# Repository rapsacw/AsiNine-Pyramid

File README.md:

# aSiNine Pyramid<br>
Schematic and layout in Eagle PCB for a quad bm1387 standalone miner<br>
// skip if deemed off topic!<br>
// Other versions made<br>
// A single BM1391 version, obsolete as information on the asic is too scarce<br>
// aSiNine Pharaonis: dual BM1387 version, compatible with the quad version (this)<br>
// Unnamed project single BM1397 (in pre-alpha stage, pcb's are on the slow boat from China)<br>
<br>
Motivation:
I'm running an ESP32C3 with a RGB LED to monitor traffic (flickers on inbound TX's and glows on memory pool size) to my node.<br>
Why not let it do something useful while idle?<br>
<br>
Properties (concept):
- Standalone miner to be connected to a mining pool or a private Bitcoin node that will serve the work (over websocket)
- Size: 80x60mm
- Programmable Vcore for the bm1387 asics
- ws2812 led for special effects ;)
- max. power usage targeted at ~10-15W
- Cooling: M.2 SSD cooler, tie-wrapped to the board with 5V fan.
- Low(est) cost possible!

Major parts used:
- 4x BM1387xx asics (tested bm1387bf & bm1387b)
- ESP32-C3-mini-1
- SY8208A or B step down regulator (8A) <s>(currently controlled by PWM, considering a cheap ($0.10) DAC)</s> controlled by a dac.
- XC6206P-18 lin. regulators for 1.8 & 0.8V
- SY8009B step down regulator (overkill) for the esp32c3, limiting the power supply to 5V only..
- usb-c connector for power (5V) and debugging

Revisions<br>
<br>* Don't build anything alpha, components and schematic/layout will change in future revisions. *<br>
v0.2-alpha (see tag) 7-12-2022 upto today<br> Not actually build/tested yet.<br>
All bugs from v0.1 corrected.<br>
Included dac to control Vcore (in 19.2uV steps, overkill).<br>
Added temperature sensor (not yet calibrated or tested).<br>
Added fan (5V only) with  pwm control.<br>
Added feedback of Vcore to the ESP32 to calibrate the power supply.<br>
No more (big) hardware changes anticipated.<br>
<s>No more (big) layout changes aticipated.</s> Ok, now though.<br>
<br>
v0.1 29-10-2022<br> Debugging stage<br>
pre alpha version<br>
(For the unpublished 2 asic version (Pharaonis): Added a pt8211 DAC to control Vcore instead of a PWM from the esp32c3, the pwm caused some problems during wifi transfers and reconnects. I'm currently working on this version, some results found during testing: power usage ~2.8W @ <s>44GH/s</s> ~40GH/s, so it can be passively cooled.)<br>
!BM1387 apparently only seaches through roughly 4000 mega nonces out of the 4.295 mega nonces available...!<br>
Function tested ok <s>but unstable (related to pwm)</s><br>
todo: <s>final speccing of decoupling capacitors, redo some of the power&ground planes, more stability testing, add dac to schematic and layout, change mounting holes for heatsink</s>.<br>

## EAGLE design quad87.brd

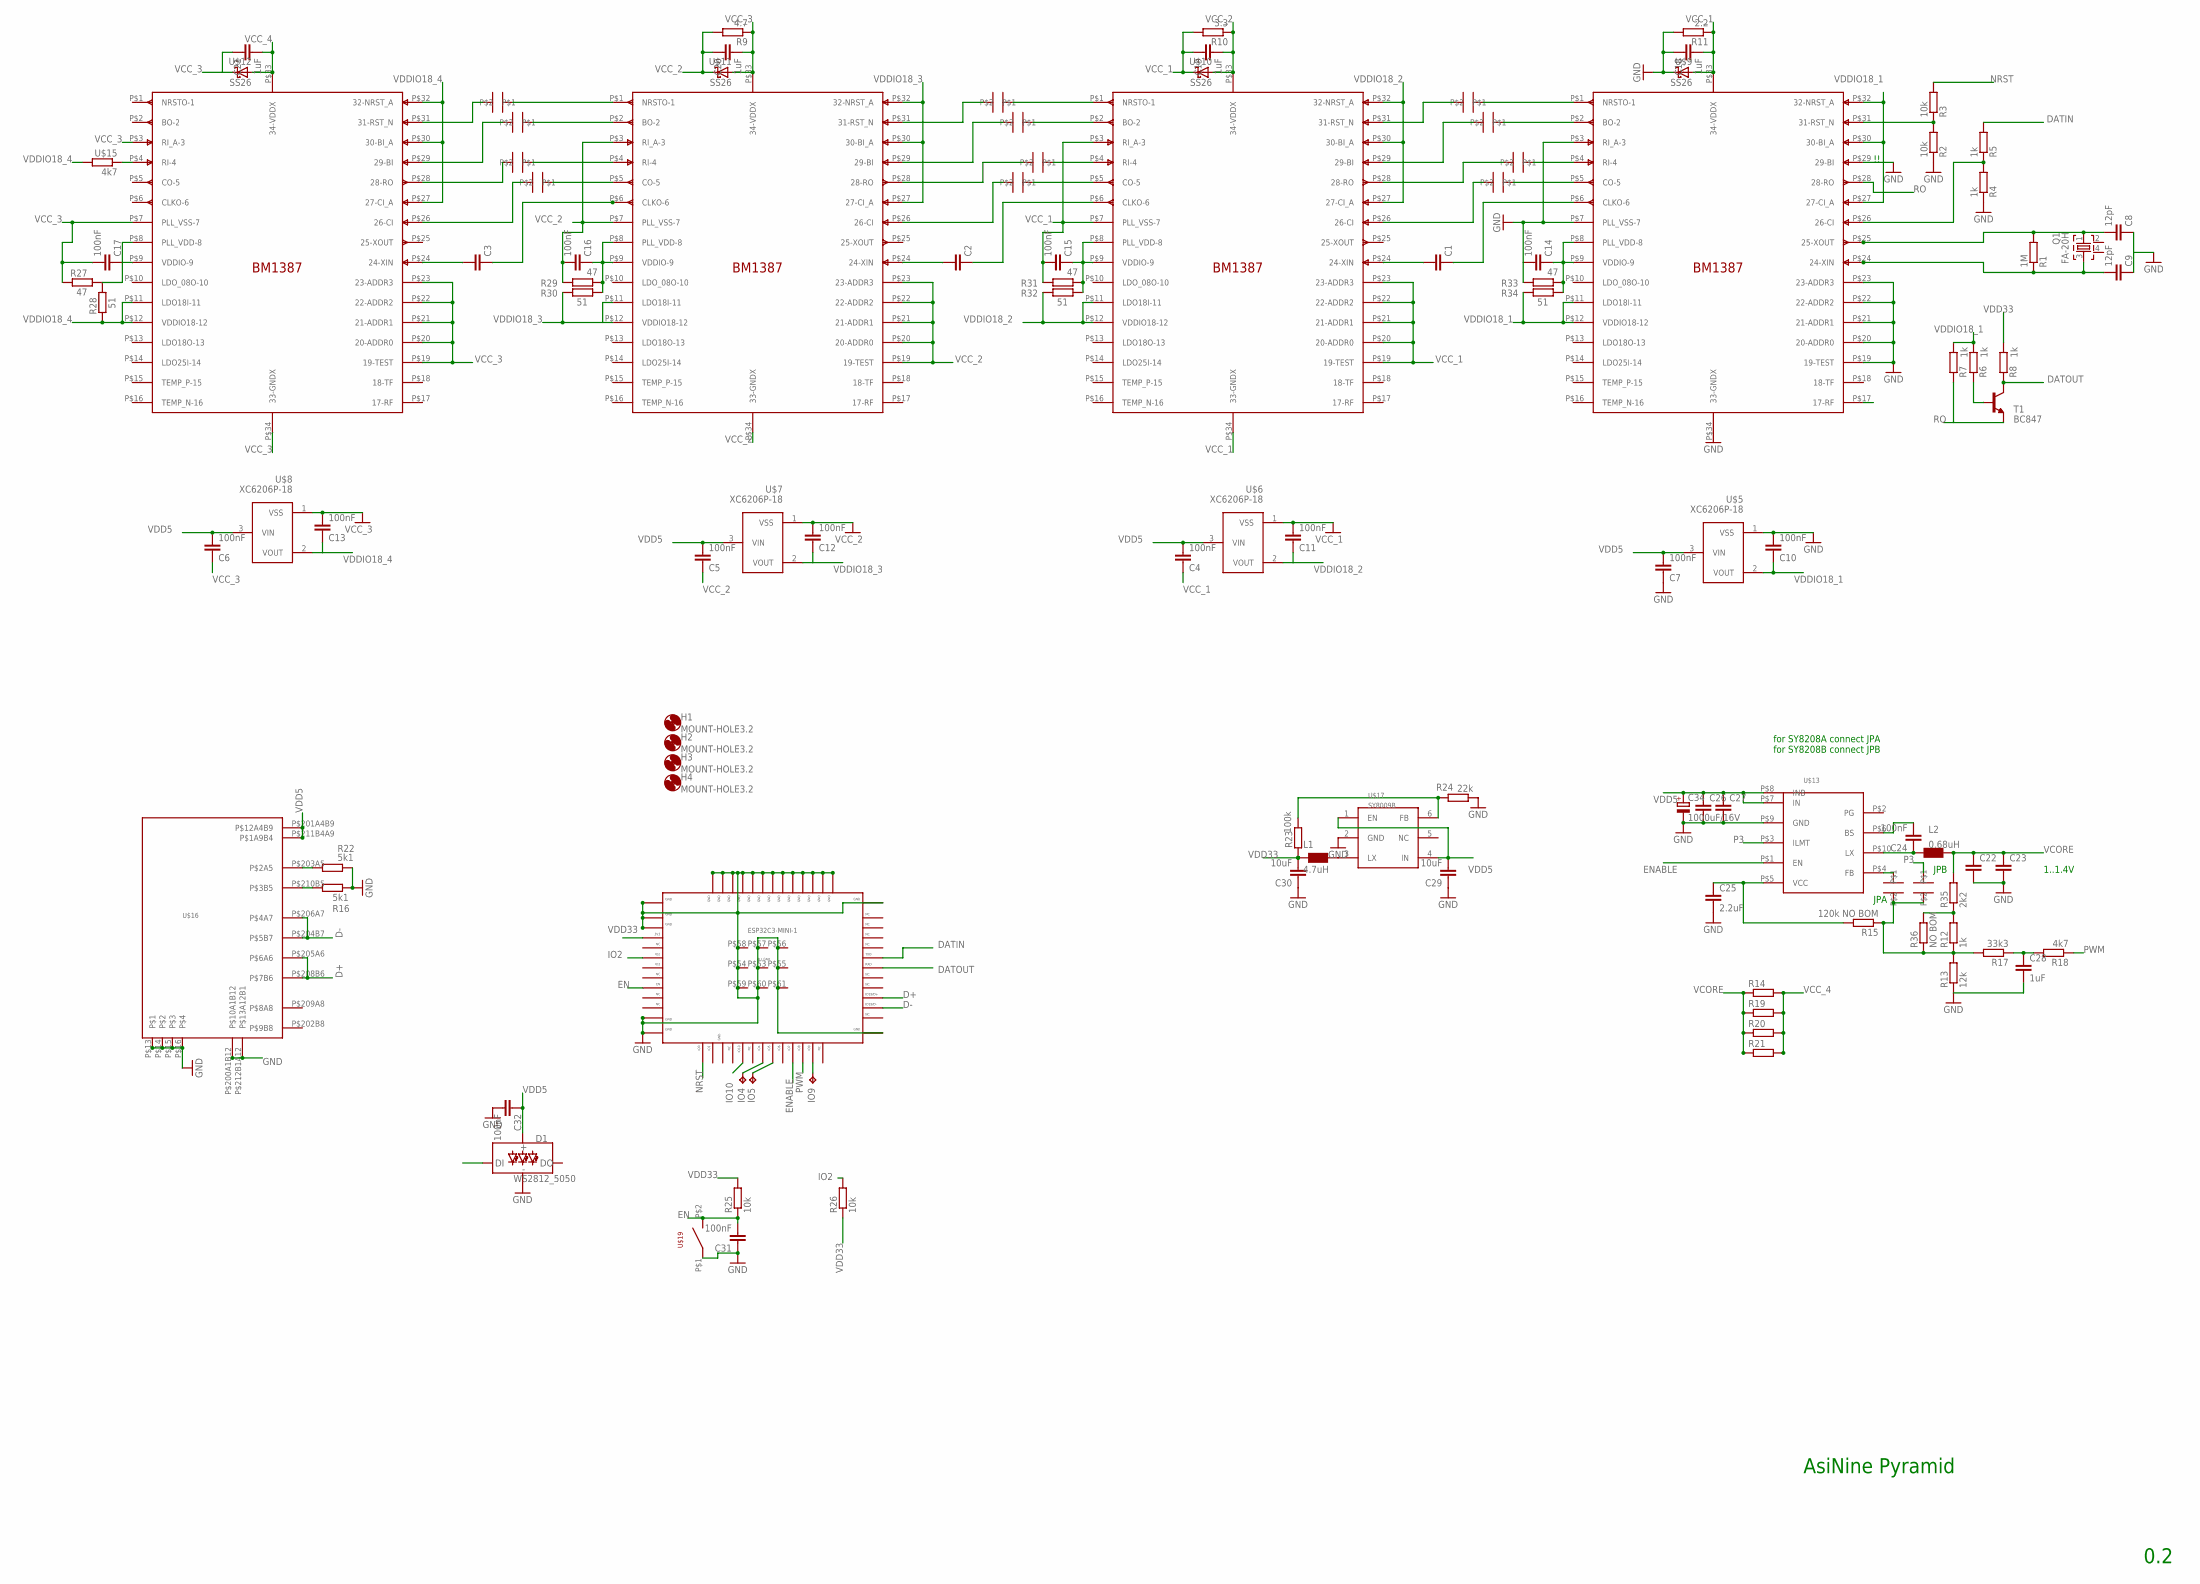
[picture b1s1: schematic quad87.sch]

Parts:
C1, C2, C3: C-EUC0402; C0402
C4, C5, C6, C7, C10, C11, C12, C13, C24, C31, C32: 100nF; C0603
C8, C9: 12pF; C0402
C14, C15, C16, C17: 100nF; C0402
C18, C19, C20, C21, C28: 1uF; C0603
C22, C23: C-EUC1210K; C1210K
C25: 2.2uF; C0603
C26, C27: C-EUC0805; C0805
C29, C30: 10uF; C0603
C34: 1000uF/16V; TT5D10
D1: WS2812_5050; WS2812-5X5-4PIN
ESP32C3-MINI-1: ESP32-C3-MINI-1; ESP32C3MINI
H1, H2, H3, H4: MOUNT-HOLE3.2; 3,2
IO4, IO5, IO9: TPB1,27; B1,27
JPA: SOLDERJUMPER
JPB: SOLDERJUMPER
L1: 4.7uH; L0420
L2: 0.68uH; L0630
Q1: FA-20H
R1: 1M; R0402
R2, R3: 10k; R0402
R4, R5, R6, R7, R8, R12: 1k; R0603
R9: 4.7; R0603
R10: 3.3; R0603
R11: 2.2; R0603
R13: 12k; R0603
R14, R19, R20, R21: R-EU_R2010; R2010
R15: 120k NO BOM; R0603
R16, R22: 5k1; R0402
R17: 33k3; R0603
R18: 4k7; R0603
R23: 100k; R0603
R24: 22k; R0603
R25, R26: 10k; R0603
R27, R29, R31, R33: 47; R0402
R28, R30, R32, R34: 51; R0402
R35: 2k2; R0603
R36: NO BOM; R0603
T1: BC847; SOT23
U$1, U$2, U$3, U$4: BM1387A; BM1391
U$5, U$6, U$7, U$8: XC6206P-18; SOT23
U$9, U$10, U$11, U$12: SS26
U$13: SY8208
U$15: 4k7; R0603
U$16: USBCTHT; USBCSMTTHT
U$17: SY8009B; SOT23-6
U$19: SMDSW6X3; SW6X3
U$20, U$21, U$22, U$23, U$24, U$25, U$26, U$28, U$29, U$30, U$31, U$32: SOLDERJUMPER

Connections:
CI: R4.2, R5.1, U$1.P$26 (26-CI)
D+: ESP32C3-MINI-1.P$27, U$16.P$205A6 (P$6A6), U$16.P$208B6 (P$7B6)
D-: ESP32C3-MINI-1.P$26, U$16.P$204B7 (P$5B7), U$16.P$206A7 (P$4A7)
DATIN: ESP32C3-MINI-1.P$31, R5.2
DATOUT: ESP32C3-MINI-1.P$30, R8.1, T1.3 (C)
EN: C31.2, ESP32C3-MINI-1.P$8, R25.1, U$19.P$2
ENABLE: ESP32C3-MINI-1.P$21, U$13.P$1 (EN)
FB: JPA.P$1, JPB.P$1, R12.1, R13.2, R15.1, R17.2, R36.1
GND: C7.1, C8.1, C9.1, C10.2, C14.2, C18.1, C22.2, C23.2, C25.2, C26.2, C27.2, C28.2, C29.1, C30.1, C31.1, C32.2, C34.-, D1.GND, ESP32C3-MINI-1.P$1, ESP32C3-MINI-1.P$2, ESP32C3-MINI-1.P$11, ESP32C3-MINI-1.P$36, ESP32C3-MINI-1.P$37, ESP32C3-MINI-1.P$38, ESP32C3-MINI-1.P$39, ESP32C3-MINI-1.P$40, ESP32C3-MINI-1.P$41, ESP32C3-MINI-1.P$42, ESP32C3-MINI-1.P$43, ESP32C3-MINI-1.P$44, ESP32C3-MINI-1.P$45, ESP32C3-MINI-1.P$46, ESP32C3-MINI-1.P$47, ESP32C3-MINI-1.P$48, ESP32C3-MINI-1.P$49, ESP32C3-MINI-1.P$50, ESP32C3-MINI-1.P$51, ESP32C3-MINI-1.P$52, ESP32C3-MINI-1.P$53, ESP32C3-MINI-1.P$54, ESP32C3-MINI-1.P$55, ESP32C3-MINI-1.P$56, ESP32C3-MINI-1.P$57, ESP32C3-MINI-1.P$58, ESP32C3-MINI-1.P$59, ESP32C3-MINI-1.P$60, ESP32C3-MINI-1.P$61, R2.1, R4.1, R11.2, R13.1, R16.2, R22.2, R24.1, R33.2, U$1.P$3 (RI_A-3), U$1.P$7 (PLL_VSS-7), U$1.P$19 (19-TEST), U$1.P$20 (20-ADDR0), U$1.P$21 (21-ADDR1), U$1.P$22 (22-ADDR2), U$1.P$23 (23-ADDR3), U$1.P$29 (29-BI), U$1.P$34 (33-GNDX), U$5.1 (VSS), U$9.P$2 (C), U$13.P$9 (GND), U$16.P$13, U$16.P$14, U$16.P$15, U$16.P$16, U$16.P$200A1B12 (P$10A1B12), U$16.P$212B1A12 (P$13A12B1), U$17.2 (GND), U$19.P$1
IO2: ESP32C3-MINI-1.P$5, R26.2
IO10: D1.DI, ESP32C3-MINI-1.P$16
unnamed: U$2.P$31 (31-RST_N), U$29.P$1
unnamed: U$3.P$31 (31-RST_N), U$24.P$1
unnamed: U$2.P$29 (29-BI), U$30.P$1
unnamed: U$3.P$29 (29-BI), U$25.P$1
unnamed: U$2.P$28 (28-RO), U$31.P$1
unnamed: U$3.P$28 (28-RO), U$26.P$1
unnamed: U$2.P$26 (26-CI), U$32.P$1
unnamed: U$3.P$26 (26-CI), U$28.P$1
unnamed: C1.1, U$1.P$6 (CLKO-6)
unnamed: C1.2, U$2.P$24 (24-XIN)
unnamed: C2.1, U$2.P$6 (CLKO-6)
unnamed: C2.2, U$3.P$24 (24-XIN)
unnamed: U$4.P$31 (31-RST_N), U$20.P$1
unnamed: U$4.P$29 (29-BI), U$21.P$1
unnamed: U$4.P$28 (28-RO), U$22.P$1
unnamed: U$4.P$26 (26-CI), U$23.P$1
unnamed: C3.1, U$3.P$6 (CLKO-6)
unnamed: C3.2, U$4.P$24 (24-XIN)
unnamed: C8.2, Q1.1, R1.2, U$1.P$25 (25-XOUT)
unnamed: C9.2, Q1.3, R1.1, U$1.P$24 (24-XIN)
unnamed: R16.1, U$16.P$210B5 (P$3B5)
unnamed: R22.1, U$16.P$203A5 (P$2A5)
unnamed: L1.P$2 (2), U$17.3 (LX)
unnamed: R23.2, R24.2, U$17.6 (FB)
unnamed: R2.2, R3.1, U$1.P$31 (31-RST_N)
unnamed: R6.1, T1.1 (B)
unnamed: R12.2, R35.1, R36.2
unnamed: C14.1, R33.1, R34.1, U$1.P$8 (PLL_VDD-8), U$1.P$9 (VDDIO-9)
unnamed: C15.1, R31.1, R32.1, U$2.P$8 (PLL_VDD-8), U$2.P$9 (VDDIO-9)
unnamed: C17.1, R27.1, R28.1, U$4.P$8 (PLL_VDD-8), U$4.P$9 (VDDIO-9)
unnamed: U$4.P$4 (RI-4), U$15.1
unnamed: JPA.P$2, U$13.P$4 (FB)
unnamed: C24.1, L2.P$1 (1), U$13.P$10 (LX)
unnamed: C24.2, U$13.P$6 (BS)
unnamed: ESP32C3-MINI-1.P$18, IO4.TP
unnamed: C28.1, R17.1, R18.2
unnamed: ESP32C3-MINI-1.P$19, IO5.TP
unnamed: ESP32C3-MINI-1.P$23, IO9.TP
unnamed: U$3.P$1 (NRSTO-1), U$20.P$2
unnamed: U$3.P$2 (BO-2), U$21.P$2
unnamed: U$3.P$4 (RI-4), U$22.P$2
unnamed: U$3.P$5 (CO-5), U$23.P$2
unnamed: U$2.P$1 (NRSTO-1), U$24.P$2
unnamed: U$2.P$2 (BO-2), U$25.P$2
unnamed: U$2.P$4 (RI-4), U$26.P$2
unnamed: U$2.P$5 (CO-5), U$28.P$2
unnamed: U$1.P$1 (NRSTO-1), U$29.P$2
unnamed: U$1.P$2 (BO-2), U$30.P$2
unnamed: U$1.P$4 (RI-4), U$31.P$2
unnamed: U$1.P$5 (CO-5), U$32.P$2
unnamed: C16.1, R29.1, R30.1, U$3.P$8 (PLL_VDD-8), U$3.P$9 (VDDIO-9)
NRST: ESP32C3-MINI-1.P$12, R3.2
P3: JPB.P$2, U$13.P$3 (ILMT)
PWM: ESP32C3-MINI-1.P$22, R18.1
RO: R7.1, T1.2 (E), U$1.P$28 (28-RO)
VCC_1: C4.1, C11.2, C15.2, C18.2, C19.1, R10.2, R11.1, R31.2, U$1.P$33 (34-VDDX), U$2.P$3 (RI_A-3), U$2.P$7 (PLL_VSS-7), U$2.P$19 (19-TEST), U$2.P$20 (20-ADDR0), U$2.P$21 (21-ADDR1), U$2.P$22 (22-ADDR2), U$2.P$23 (23-ADDR3), U$2.P$34 (33-GNDX), U$6.1 (VSS), U$9.P$1 (A), U$10.P$2 (C)
VCC_2: C5.1, C12.2, C16.2, C19.2, C20.1, R9.2, R10.1, R29.2, U$2.P$33 (34-VDDX), U$3.P$3 (RI_A-3), U$3.P$7 (PLL_VSS-7), U$3.P$19 (19-TEST), U$3.P$20 (20-ADDR0), U$3.P$21 (21-ADDR1), U$3.P$22 (22-ADDR2), U$3.P$23 (23-ADDR3), U$3.P$34 (33-GNDX), U$7.1 (VSS), U$10.P$1 (A), U$11.P$2 (C)
VCC_3: C6.1, C13.2, C17.2, C20.2, C21.1, R9.1, R27.2, U$3.P$33 (34-VDDX), U$4.P$3 (RI_A-3), U$4.P$7 (PLL_VSS-7), U$4.P$19 (19-TEST), U$4.P$20 (20-ADDR0), U$4.P$21 (21-ADDR1), U$4.P$22 (22-ADDR2), U$4.P$23 (23-ADDR3), U$4.P$34 (33-GNDX), U$8.1 (VSS), U$11.P$1 (A), U$12.P$2 (C)
VCC_4: C21.2, R14.2, R19.2, R20.2, R21.2, U$4.P$33 (34-VDDX), U$12.P$1 (A)
VCORE: C22.1, C23.1, L2.P$2 (2), R14.1, R19.1, R20.1, R21.1, R35.2
VDD5: C4.2, C5.2, C6.2, C7.2, C26.1, C27.1, C29.2, C32.1, C34.+, D1.VCC, U$5.3 (VIN), U$6.3 (VIN), U$7.3 (VIN), U$8.3 (VIN), U$13.P$7 (IN), U$13.P$8 (INB), U$16.P$201A4B9 (P$12A4B9), U$16.P$211B4A9 (P$1A9B4), U$17.1 (EN), U$17.4 (IN)
VDD33: C30.2, ESP32C3-MINI-1.P$3, L1.P$1 (1), R8.2, R23.1, R25.2, R26.1
VDD33I: C25.1, R15.2, U$13.P$5 (VCC)
VDDIO18_1: C10.1, R6.2, R7.2, R34.2, U$1.P$11 (LDO18I-11), U$1.P$12 (VDDIO18-12), U$1.P$27 (27-CI_A), U$1.P$30 (30-BI_A), U$1.P$32 (32-NRST_A), U$5.2 (VOUT)
VDDIO18_2: C11.1, R32.2, U$2.P$11 (LDO18I-11), U$2.P$12 (VDDIO18-12), U$2.P$27 (27-CI_A), U$2.P$30 (30-BI_A), U$2.P$32 (32-NRST_A), U$6.2 (VOUT)
VDDIO18_3: C12.1, R30.2, U$3.P$11 (LDO18I-11), U$3.P$12 (VDDIO18-12), U$3.P$27 (27-CI_A), U$3.P$30 (30-BI_A), U$3.P$32 (32-NRST_A), U$7.2 (VOUT)
VDDIO18_4: C13.1, R28.2, U$4.P$11 (LDO18I-11), U$4.P$12 (VDDIO18-12), U$4.P$27 (27-CI_A), U$4.P$30 (30-BI_A), U$4.P$32 (32-NRST_A), U$8.2 (VOUT), U$15.2

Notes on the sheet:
for SY8208A connect JPA for SY8208B connect JPB
1..1.4V
JPA
JPB
AsiNine Pyramid
0.2

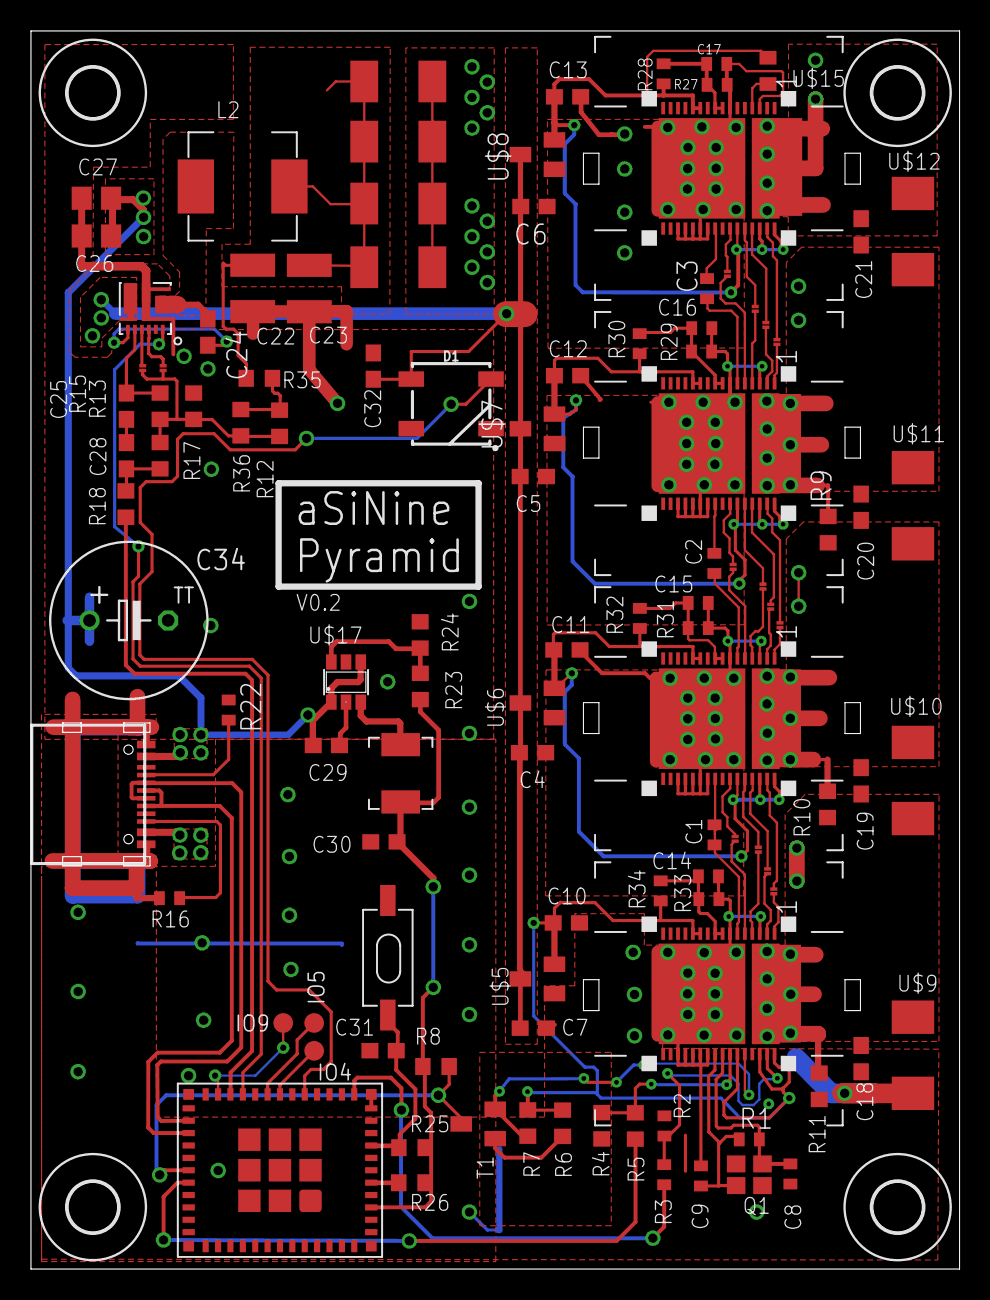
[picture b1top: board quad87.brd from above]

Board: 2 copper layers, 60.0 x 80.0 mm, 113 parts (0 on the bottom side), 78 nets.

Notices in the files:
parts and their libraries:
SparkFun-LED: Licensing: Creative Commons ShareAlike 4.0 International - https://creativecommons.org/licenses/by-sa/4.0
